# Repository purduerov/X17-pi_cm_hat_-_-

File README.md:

# X17-pi_cm_hat_-_-
Raspberry pi compute module 4 R&amp;D  board.

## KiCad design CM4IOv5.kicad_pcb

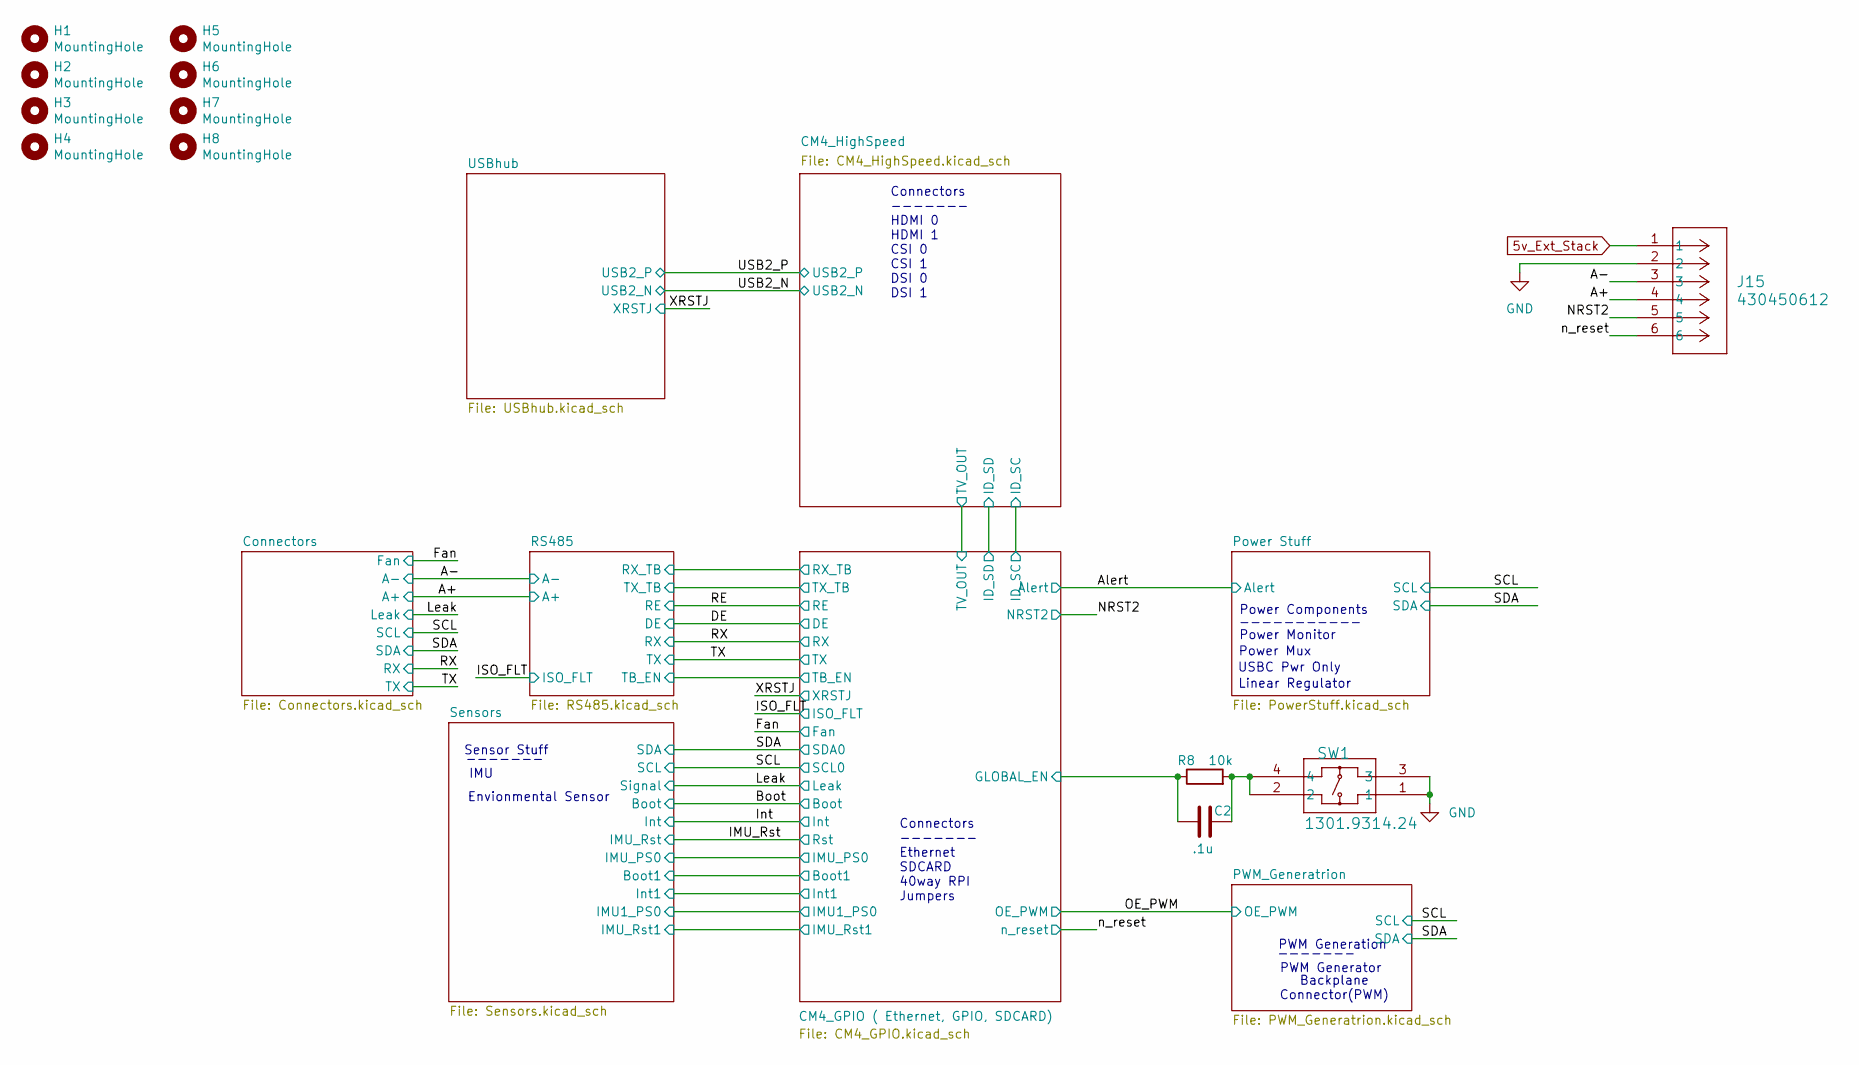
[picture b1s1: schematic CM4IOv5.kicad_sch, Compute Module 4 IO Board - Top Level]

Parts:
C2: .1u; C_0805_2012Metric
H1, H2, H3, H4, H5, H6, H7, H8: MountingHole; MountingHole_2.7mm_M2.5; Part Description M2.5 mounting hole
J15: 430450612; CON_430450612_MOL
R8: 10k; R_0805_2012Metric
SW1: 1301.9314.24; 1301.9314.24_SCH

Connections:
5v_Ext_Stack: J15.1; also elsewhere on the board
/A+: J15.4; also elsewhere on the board
/A-: J15.3; also elsewhere on the board
/CM4_GPIO ( Ethernet, GPIO, SDCARD)/GLOBAL_EN: C2.1, R8.1; also elsewhere on the board
/NRST2: J15.5; also elsewhere on the board
/n_reset: J15.6; also elsewhere on the board
GND: J15.2, SW1.1, SW1.3; also elsewhere on the board
unnamed: C2.2, R8.2, SW1.2, SW1.4

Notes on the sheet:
Power Mux
-----------
PWM Generation
Power Components
Envionmental Sensor
IMU
USBC Pwr Only
Sensor Stuff
-------
Connectors ------- Ethernet SDCARD 40way RPI Jumpers
Connectors ------- HDMI 0 HDMI 1 CSI 0 CSI 1 DSI 0 DSI 1
Backplane Connector(PWM)
PWM Generator
Linear Regulator
Power Monitor

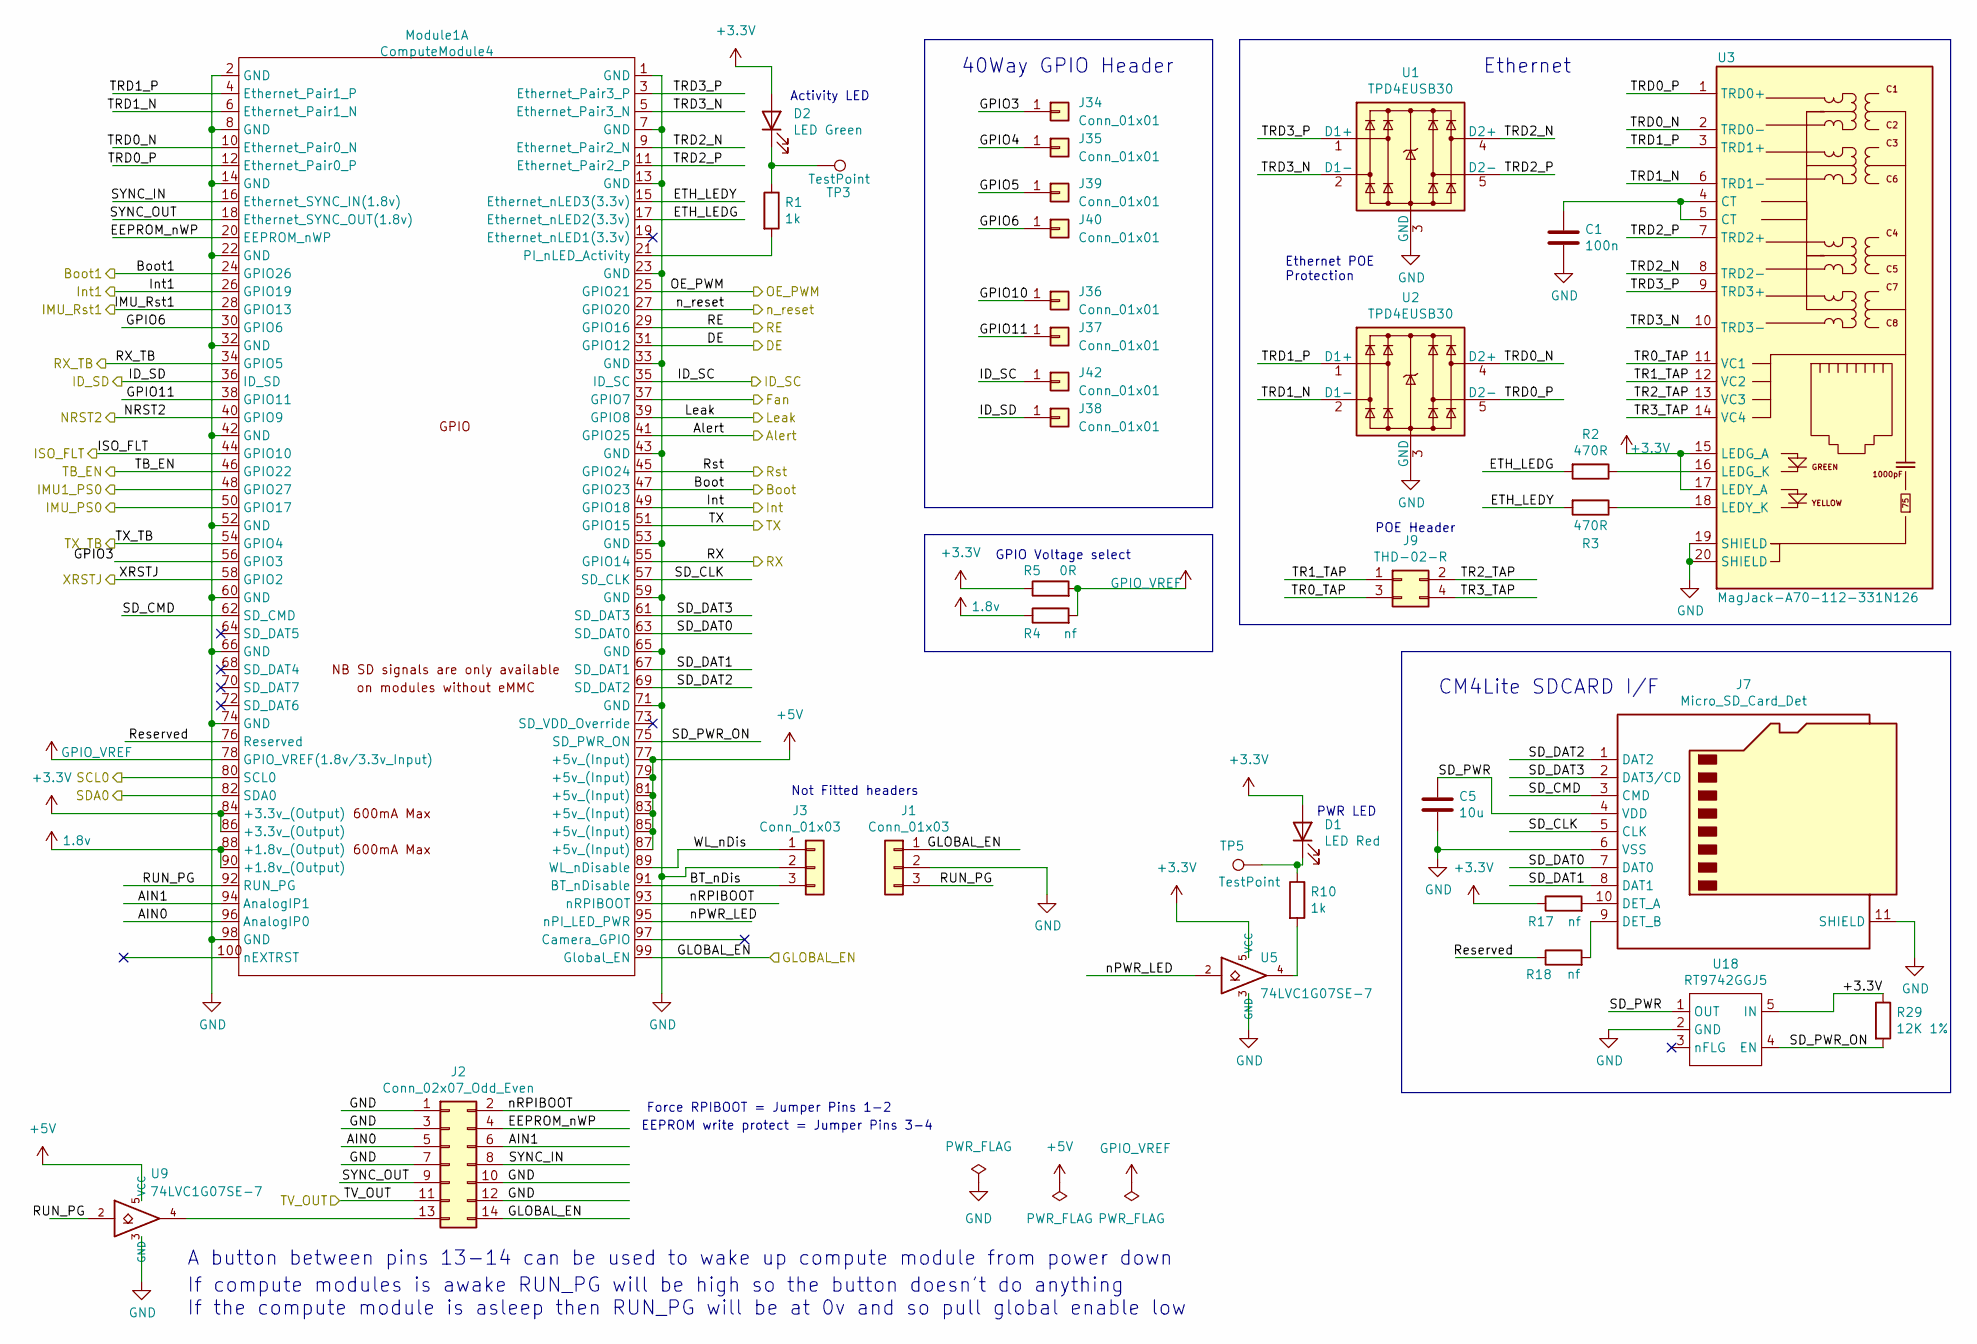
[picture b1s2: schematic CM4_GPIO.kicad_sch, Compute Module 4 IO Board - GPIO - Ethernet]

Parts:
C1: 100n; C_0805_2012Metric; Part Description 0.1uF 10% 16V Ceramic Capacitor X7R 040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
C5: 10u; C_0805_2012Metric; Part Description 10uF 10% 10V Ceramic Capacitor X7R 0805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
D1: LED Red; LED_0805_2012Metric; Part Description Red 620nm LED Indication - Discrete 2.2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
D2: LED Green; LED_0805_2012Metric; Part Description Green 572nm LED Indication - Discrete 2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
J1, J3: Conn_01x03; PinHeader_1x03_P2.54mm_Vertical; Part Description 3pin 0.1" connector
J2: Conn_02x07_Odd_Even; PinHeader_2x07_P2.54mm_Vertical; Part Description PinHeader_2x07_P2.54mm_Vertical
J7: Micro_SD_Card_Det; SDCARD_MOLEX_503398-1892; Part Description 9 (8 + 1) Position Card Connector micro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
J9: THD-02-R; PinHeader_2x02_P2.54mm_Vertical; Part Description PinHeader_2x02_P2.54mm_Vertical
J34, J35, J36, J37, J38, J39, J40, J42: Conn_01x01; PinHeader_1x01_P2.54mm_Vertical
Module1: ComputeModule4; Raspberry-Pi-4-Compute-Module; Part Description 100 Position Connector Receptacle, Cent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
R1, R10: 1k; R_0805_2012Metric; Part Description Resistor 1K M1005 1% 63mW
R2, R3: 470R; R_0805_2012Metric; Part Description Resistor 470R M1005 1% 63mW
R4: nf; R_0805_2012Metric
R5: 0R; R_0805_2012Metric; Part Description Resistor 0R M2012 5%
R17, R18: nf; R_0805_2012Metric; Part Description Resistor 1K M1005 1% 63mW
R29: 12K 1%; R_0805_2012Metric; Part Description Resistor 12K M1005 1% 63mW
TP3, TP5: TestPoint; TestPoint_Plated_Hole_D3.0mm
U1, U2: TPD4EUSB30; USON-10_2.5x1.0mm_P0.5mm; Part Description Quad TVS diode for high speed signals (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
U3: MagJack-A70-112-331N126; TRJG0926HENL; Part Description Gigabit Ethernet Magjack
U5, U9: 74LVC1G07SE-7; SOT-353_SC-70-5; Part Description Buffer, Non-Inverting 1 Element 1 Bit p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
U18: RT9742GGJ5; SOT-23-5; Part Description Power Switch/Driver 1:1 N-Channel 1A TS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

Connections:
1.8v: Module1.88 (+1.8v_(Output)), Module1.90 (+1.8v_(Output)), R4.1
+3.3V: D1.2 (A), D2.2 (A), Module1.84 (+3.3v_(Output)), Module1.86 (+3.3v_(Output)), R5.1, R17.1, R29.1, U3.15 (LEDG_A), U3.17 (LEDY_A), U5.5 (VCC), U18.5 (IN); also elsewhere on the board
+5V: Module1.77 (+5v_(Input)), Module1.79 (+5v_(Input)), Module1.81 (+5v_(Input)), Module1.83 (+5v_(Input)), Module1.85 (+5v_(Input)), Module1.87 (+5v_(Input)), U9.5 (VCC); also elsewhere on the board
/Alert: Module1.41 (GPIO25); also elsewhere on the board
/Boot: Module1.47 (GPIO23); also elsewhere on the board
/CM4_GPIO ( Ethernet, GPIO, SDCARD)/AIN0: J2.5, Module1.96 (AnalogIP0)
/CM4_GPIO ( Ethernet, GPIO, SDCARD)/AIN1: J2.6, Module1.94 (AnalogIP1)
/CM4_GPIO ( Ethernet, GPIO, SDCARD)/BT_nDis: J3.3, Module1.91 (BT_nDisable)
/CM4_GPIO ( Ethernet, GPIO, SDCARD)/Boot1: Module1.24 (GPIO26); also elsewhere on the board
/CM4_GPIO ( Ethernet, GPIO, SDCARD)/EEPROM_nWP: J2.4, Module1.20 (EEPROM_nWP)
/CM4_GPIO ( Ethernet, GPIO, SDCARD)/ETH_LEDG: Module1.17 (Ethernet_nLED2(3.3v)), R2.2
/CM4_GPIO ( Ethernet, GPIO, SDCARD)/ETH_LEDY: Module1.15 (Ethernet_nLED3(3.3v)), R3.2
/CM4_GPIO ( Ethernet, GPIO, SDCARD)/GLOBAL_EN: J1.1, J2.14, Module1.99 (Global_EN); also elsewhere on the board
/CM4_GPIO ( Ethernet, GPIO, SDCARD)/GPIO3: J34.1, Module1.56 (GPIO3)
/CM4_GPIO ( Ethernet, GPIO, SDCARD)/GPIO6: J40.1, Module1.30 (GPIO6)
/CM4_GPIO ( Ethernet, GPIO, SDCARD)/GPIO11: J37.1, Module1.38 (GPIO11)
/CM4_GPIO ( Ethernet, GPIO, SDCARD)/ID_SC: J42.1, Module1.35 (ID_SC); also elsewhere on the board
/CM4_GPIO ( Ethernet, GPIO, SDCARD)/ID_SD: J38.1, Module1.36 (ID_SD); also elsewhere on the board
/CM4_GPIO ( Ethernet, GPIO, SDCARD)/IMU1_PS0: Module1.48 (GPIO27); also elsewhere on the board
/CM4_GPIO ( Ethernet, GPIO, SDCARD)/IMU_PS0: Module1.50 (GPIO17); also elsewhere on the board
/CM4_GPIO ( Ethernet, GPIO, SDCARD)/IMU_Rst1: Module1.28 (GPIO13); also elsewhere on the board
/CM4_GPIO ( Ethernet, GPIO, SDCARD)/Int1: Module1.26 (GPIO19); also elsewhere on the board
/CM4_GPIO ( Ethernet, GPIO, SDCARD)/RUN_PG: J1.3, Module1.92 (RUN_PG), U9.2
/CM4_GPIO ( Ethernet, GPIO, SDCARD)/RX_TB: Module1.34 (GPIO5); also elsewhere on the board
/CM4_GPIO ( Ethernet, GPIO, SDCARD)/Reserved: Module1.76 (Reserved), R18.1
/CM4_GPIO ( Ethernet, GPIO, SDCARD)/SD_CLK: J7.5 (CLK), Module1.57 (SD_CLK)
/CM4_GPIO ( Ethernet, GPIO, SDCARD)/SD_CMD: J7.3 (CMD), Module1.62 (SD_CMD)
/CM4_GPIO ( Ethernet, GPIO, SDCARD)/SD_DAT0: J7.7 (DAT0), Module1.63 (SD_DAT0)
/CM4_GPIO ( Ethernet, GPIO, SDCARD)/SD_DAT1: J7.8 (DAT1), Module1.67 (SD_DAT1)
/CM4_GPIO ( Ethernet, GPIO, SDCARD)/SD_DAT2: J7.1 (DAT2), Module1.69 (SD_DAT2)
/CM4_GPIO ( Ethernet, GPIO, SDCARD)/SD_DAT3: J7.2 (DAT3/CD), Module1.61 (SD_DAT3)
/CM4_GPIO ( Ethernet, GPIO, SDCARD)/SD_PWR: C5.1, J7.4 (VDD), U18.1 (OUT)
/CM4_GPIO ( Ethernet, GPIO, SDCARD)/SD_PWR_ON: Module1.75 (SD_PWR_ON), R29.2, U18.4 (EN)
/CM4_GPIO ( Ethernet, GPIO, SDCARD)/SYNC_IN: J2.8, Module1.16 (Ethernet_SYNC_IN(1.8v))
/CM4_GPIO ( Ethernet, GPIO, SDCARD)/SYNC_OUT: J2.9, Module1.18 (Ethernet_SYNC_OUT(1.8v))
/CM4_GPIO ( Ethernet, GPIO, SDCARD)/TB_EN: Module1.46 (GPIO22); also elsewhere on the board
/CM4_GPIO ( Ethernet, GPIO, SDCARD)/TR0_TAP: J9.3, U3.11 (VC1)
/CM4_GPIO ( Ethernet, GPIO, SDCARD)/TR1_TAP: J9.1, U3.12 (VC2)
/CM4_GPIO ( Ethernet, GPIO, SDCARD)/TR2_TAP: J9.2, U3.13 (VC3)
/CM4_GPIO ( Ethernet, GPIO, SDCARD)/TR3_TAP: J9.4, U3.14 (VC4)
/CM4_GPIO ( Ethernet, GPIO, SDCARD)/TRD0_N: Module1.10 (Ethernet_Pair0_N), U2.4 (D2+), U2.7, U3.2 (TRD0-)
/CM4_GPIO ( Ethernet, GPIO, SDCARD)/TRD0_P: Module1.12 (Ethernet_Pair0_P), U2.5 (D2-), U2.6, U3.1 (TRD0+)
/CM4_GPIO ( Ethernet, GPIO, SDCARD)/TRD1_N: Module1.6 (Ethernet_Pair1_N), U2.2 (D1-), U2.9, U3.6 (TRD1-)
/CM4_GPIO ( Ethernet, GPIO, SDCARD)/TRD1_P: Module1.4 (Ethernet_Pair1_P), U2.1 (D1+), U2.10, U3.3 (TRD1+)
/CM4_GPIO ( Ethernet, GPIO, SDCARD)/TRD2_N: Module1.9 (Ethernet_Pair2_N), U1.4 (D2+), U1.7, U3.8 (TRD2-)
/CM4_GPIO ( Ethernet, GPIO, SDCARD)/TRD2_P: Module1.11 (Ethernet_Pair2_P), U1.5 (D2-), U1.6, U3.7 (TRD2+)
/CM4_GPIO ( Ethernet, GPIO, SDCARD)/TRD3_N: Module1.5 (Ethernet_Pair3_N), U1.2 (D1-), U1.9, U3.10 (TRD3-)
/CM4_GPIO ( Ethernet, GPIO, SDCARD)/TRD3_P: Module1.3 (Ethernet_Pair3_P), U1.1 (D1+), U1.10, U3.9 (TRD3+)
/CM4_GPIO ( Ethernet, GPIO, SDCARD)/TV_OUT: J2.11; also elsewhere on the board
/CM4_GPIO ( Ethernet, GPIO, SDCARD)/TX_TB: Module1.54 (GPIO4); also elsewhere on the board
/CM4_GPIO ( Ethernet, GPIO, SDCARD)/WL_nDis: J3.1, Module1.89 (WL_nDisable)
/CM4_GPIO ( Ethernet, GPIO, SDCARD)/nPWR_LED: Module1.95 (nPI_LED_PWR), U5.2
/CM4_GPIO ( Ethernet, GPIO, SDCARD)/nRPIBOOT: J2.2, Module1.93 (nRPIBOOT)
/DE: Module1.31 (GPIO12); also elsewhere on the board
/Fan: Module1.37 (GPIO7); also elsewhere on the board
/IMU_Rst: Module1.45 (GPIO24); also elsewhere on the board
/ISO_FLT: Module1.44 (GPIO10); also elsewhere on the board
/Int: Module1.49 (GPIO18); also elsewhere on the board
/Leak: Module1.39 (GPIO8); also elsewhere on the board
/NRST2: Module1.40 (GPIO9); also elsewhere on the board
/OE_PWM: Module1.25 (GPIO21); also elsewhere on the board
/RE: Module1.29 (GPIO16); also elsewhere on the board
/RX: Module1.55 (GPIO14); also elsewhere on the board
/SCL: Module1.80 (SCL0); also elsewhere on the board
/SDA: Module1.82 (SDA0); also elsewhere on the board
/TX: Module1.51 (GPIO15); also elsewhere on the board
/XRSTJ: Module1.58 (GPIO2); also elsewhere on the board
/n_reset: Module1.27 (GPIO20); also elsewhere on the board
GND: C1.2, C5.2, J1.2, J2.1, J2.3, J2.7, J2.10, J2.12, J3.2, J7.6 (VSS), J7.11 (SHIELD), Module1.1 (GND), Module1.2 (GND), Module1.7 (GND), Module1.8 (GND), Module1.13 (GND), Module1.14 (GND), Module1.22 (GND), Module1.23 (GND), Module1.32 (GND), Module1.33 (GND), Module1.42 (GND), Module1.43 (GND), Module1.52 (GND), Module1.53 (GND), Module1.59 (GND), Module1.60 (GND), Module1.65 (GND), Module1.66 (GND), Module1.71 (GND), Module1.74 (GND), Module1.98 (GND), U1.3 (GND), U1.8 (GND), U2.3 (GND), U2.8 (GND), U3.19 (SHIELD), U3.20 (SHIELD), U5.3 (GND), U9.3 (GND), U18.2 (GND); also elsewhere on the board
GPIO_VREF: Module1.78 (GPIO_VREF(1.8v/3.3v_Input)), R4.2, R5.2; also elsewhere on the board
unnamed: C1.1, U3.4 (CT), U3.5 (CT)
unnamed: D1.1 (K), R10.1, TP5.1
unnamed: D2.1 (K), R1.1, TP3.1
unnamed: J2.13, U9.4
unnamed: J7.10 (DET_A), R17.2
unnamed: J7.9 (DET_B), R18.2
unnamed: Module1.21 (PI_nLED_Activity), R1.2
unnamed: R10.2, U5.4
unnamed: R2.1, U3.16 (LEDG_K)
unnamed: R3.1, U3.18 (LEDY_K)

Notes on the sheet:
PWR LED
Ethernet POE Protection
40Way GPIO Header
CM4Lite SDCARD I/F
GPIO Voltage select
Ethernet
Activity LED
EEPROM write protect = Jumper Pins 3-4
Not Fitted headers
A button between pins 13-14 can be used to wake up compute module from power down
If compute modules is awake RUN_PG will be high so the button doesn't do anything If the compute module is asleep then RUN_PG will be at 0v and so pull global enable low
Force RPIBOOT = Jumper Pins 1-2
POE Header

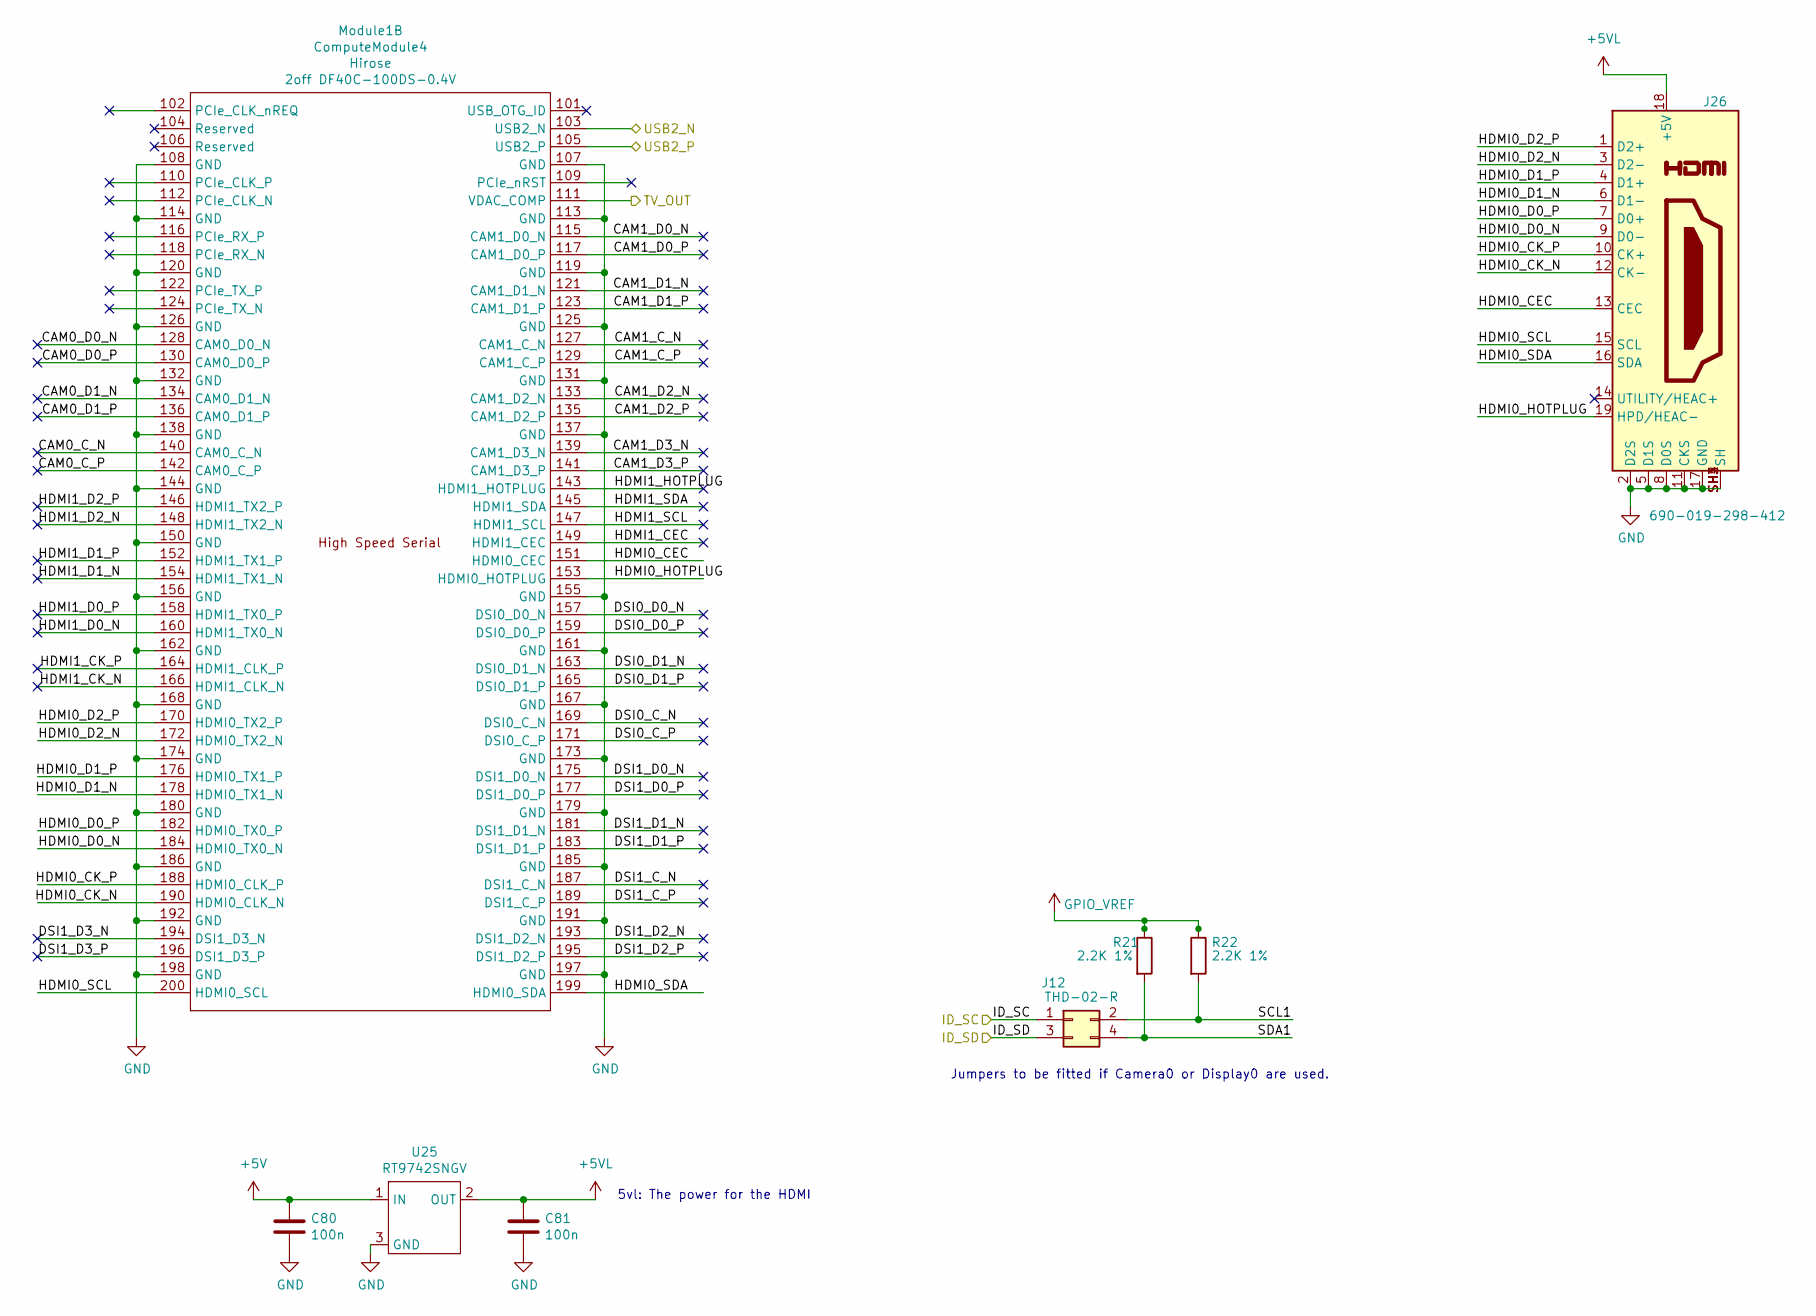
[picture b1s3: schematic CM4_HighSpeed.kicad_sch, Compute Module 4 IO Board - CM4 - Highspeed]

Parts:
C80, C81: 100n; C_0805_2012Metric; Part Description 0.1uF 10% 16V Ceramic Capacitor X7R 040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
J12: THD-02-R; PinHeader_2x02_P2.54mm_Vertical; Part Description PinHeader_2x02_P2.54mm_Vertical
J26: 690-019-298-412; EDAC 690-019-298-412; Part Description HDMI Connector, Right Angle, 19 Contact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
Module1: ComputeModule4; Raspberry-Pi-4-Compute-Module; Part Description 100 Position Connector Receptacle, Cent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
R21, R22: 2.2K 1%; R_0805_2012Metric; Part Description Resistor 2.2K M1005 1% 63mW
U25: RT9742SNGV; SOT-23; Part Description Power Switch/Driver 1:1 N-Channel 500mA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

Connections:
+5V: C80.1, U25.1 (IN); also elsewhere on the board
+5VL: C81.1, J26.18 (+5V), U25.2 (OUT)
/CM4_GPIO ( Ethernet, GPIO, SDCARD)/ID_SC: J12.1; also elsewhere on the board
/CM4_GPIO ( Ethernet, GPIO, SDCARD)/ID_SD: J12.3; also elsewhere on the board
/CM4_GPIO ( Ethernet, GPIO, SDCARD)/TV_OUT: Module1.111 (VDAC_COMP); also elsewhere on the board
/CM4_HighSpeed/CAM0_C_N: Module1.140 (CAM0_C_N)
/CM4_HighSpeed/CAM0_C_P: Module1.142 (CAM0_C_P)
/CM4_HighSpeed/CAM0_D0_N: Module1.128 (CAM0_D0_N)
/CM4_HighSpeed/CAM0_D0_P: Module1.130 (CAM0_D0_P)
/CM4_HighSpeed/CAM0_D1_N: Module1.134 (CAM0_D1_N)
/CM4_HighSpeed/CAM0_D1_P: Module1.136 (CAM0_D1_P)
/CM4_HighSpeed/CAM1_C_N: Module1.127 (CAM1_C_N)
/CM4_HighSpeed/CAM1_C_P: Module1.129 (CAM1_C_P)
/CM4_HighSpeed/CAM1_D0_N: Module1.115 (CAM1_D0_N)
/CM4_HighSpeed/CAM1_D0_P: Module1.117 (CAM1_D0_P)
/CM4_HighSpeed/CAM1_D1_N: Module1.121 (CAM1_D1_N)
/CM4_HighSpeed/CAM1_D1_P: Module1.123 (CAM1_D1_P)
/CM4_HighSpeed/CAM1_D2_N: Module1.133 (CAM1_D2_N)
/CM4_HighSpeed/CAM1_D2_P: Module1.135 (CAM1_D2_P)
/CM4_HighSpeed/CAM1_D3_N: Module1.139 (CAM1_D3_N)
/CM4_HighSpeed/CAM1_D3_P: Module1.141 (CAM1_D3_P)
/CM4_HighSpeed/DSI0_C_N: Module1.169 (DSI0_C_N)
/CM4_HighSpeed/DSI0_C_P: Module1.171 (DSI0_C_P)
/CM4_HighSpeed/DSI0_D0_N: Module1.157 (DSI0_D0_N)
/CM4_HighSpeed/DSI0_D0_P: Module1.159 (DSI0_D0_P)
/CM4_HighSpeed/DSI0_D1_N: Module1.163 (DSI0_D1_N)
/CM4_HighSpeed/DSI0_D1_P: Module1.165 (DSI0_D1_P)
/CM4_HighSpeed/DSI1_C_N: Module1.187 (DSI1_C_N)
/CM4_HighSpeed/DSI1_C_P: Module1.189 (DSI1_C_P)
/CM4_HighSpeed/DSI1_D0_N: Module1.175 (DSI1_D0_N)
/CM4_HighSpeed/DSI1_D0_P: Module1.177 (DSI1_D0_P)
/CM4_HighSpeed/DSI1_D1_N: Module1.181 (DSI1_D1_N)
/CM4_HighSpeed/DSI1_D1_P: Module1.183 (DSI1_D1_P)
/CM4_HighSpeed/DSI1_D2_N: Module1.193 (DSI1_D2_N)
/CM4_HighSpeed/DSI1_D2_P: Module1.195 (DSI1_D2_P)
/CM4_HighSpeed/DSI1_D3_N: Module1.194 (DSI1_D3_N)
/CM4_HighSpeed/DSI1_D3_P: Module1.196 (DSI1_D3_P)
/CM4_HighSpeed/HDMI0_CEC: J26.13 (CEC), Module1.151 (HDMI0_CEC)
/CM4_HighSpeed/HDMI0_CK_N: J26.12 (CK-), Module1.190 (HDMI0_CLK_N)
/CM4_HighSpeed/HDMI0_CK_P: J26.10 (CK+), Module1.188 (HDMI0_CLK_P)
/CM4_HighSpeed/HDMI0_D0_N: J26.9 (D0-), Module1.184 (HDMI0_TX0_N)
/CM4_HighSpeed/HDMI0_D0_P: J26.7 (D0+), Module1.182 (HDMI0_TX0_P)
/CM4_HighSpeed/HDMI0_D1_N: J26.6 (D1-), Module1.178 (HDMI0_TX1_N)
/CM4_HighSpeed/HDMI0_D1_P: J26.4 (D1+), Module1.176 (HDMI0_TX1_P)
/CM4_HighSpeed/HDMI0_D2_N: J26.3 (D2-), Module1.172 (HDMI0_TX2_N)
/CM4_HighSpeed/HDMI0_D2_P: J26.1 (D2+), Module1.170 (HDMI0_TX2_P)
/CM4_HighSpeed/HDMI0_HOTPLUG: J26.19 (HPD/HEAC-), Module1.153 (HDMI0_HOTPLUG)
/CM4_HighSpeed/HDMI0_SCL: J26.15 (SCL), Module1.200 (HDMI0_SCL)
/CM4_HighSpeed/HDMI0_SDA: J26.16 (SDA), Module1.199 (HDMI0_SDA)
/CM4_HighSpeed/HDMI1_CEC: Module1.149 (HDMI1_CEC)
/CM4_HighSpeed/HDMI1_CK_N: Module1.166 (HDMI1_CLK_N)
/CM4_HighSpeed/HDMI1_CK_P: Module1.164 (HDMI1_CLK_P)
/CM4_HighSpeed/HDMI1_D0_N: Module1.160 (HDMI1_TX0_N)
/CM4_HighSpeed/HDMI1_D0_P: Module1.158 (HDMI1_TX0_P)
/CM4_HighSpeed/HDMI1_D1_N: Module1.154 (HDMI1_TX1_N)
/CM4_HighSpeed/HDMI1_D1_P: Module1.152 (HDMI1_TX1_P)
/CM4_HighSpeed/HDMI1_D2_N: Module1.148 (HDMI1_TX2_N)
/CM4_HighSpeed/HDMI1_D2_P: Module1.146 (HDMI1_TX2_P)
/CM4_HighSpeed/HDMI1_HOTPLUG: Module1.143 (HDMI1_HOTPLUG)
/CM4_HighSpeed/HDMI1_SCL: Module1.147 (HDMI1_SCL)
/CM4_HighSpeed/HDMI1_SDA: Module1.145 (HDMI1_SDA)
/CM4_HighSpeed/SCL1: J12.2, R22.2
/CM4_HighSpeed/SDA1: J12.4, R21.2
/USB2_N: Module1.103 (USB2_N); also elsewhere on the board
/USB2_P: Module1.105 (USB2_P); also elsewhere on the board
GND: C80.2, C81.2, J26.2 (D2S), J26.5 (D1S), J26.8 (D0S), J26.11 (CKS), J26.17 (GND), J26.SH1 (SH), J26.SH2 (SH), J26.SH3 (SH), J26.SH4 (SH), Module1.107 (GND), Module1.108 (GND), Module1.113 (GND), Module1.114 (GND), Module1.119 (GND), Module1.120 (GND), Module1.125 (GND), Module1.126 (GND), Module1.131 (GND), Module1.132 (GND), Module1.137 (GND), Module1.138 (GND), Module1.144 (GND), Module1.150 (GND), Module1.155 (GND), Module1.156 (GND), Module1.161 (GND), Module1.162 (GND), Module1.167 (GND), Module1.168 (GND), Module1.173 (GND), Module1.174 (GND), Module1.179 (GND), Module1.180 (GND), Module1.185 (GND), Module1.186 (GND), Module1.191 (GND), Module1.192 (GND), Module1.197 (GND), Module1.198 (GND), U25.3 (GND); also elsewhere on the board
GPIO_VREF: R21.1, R22.1; also elsewhere on the board

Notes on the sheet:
Jumpers to be fitted if Camera0 or Display0 are used.
5vl: The power for the HDMI

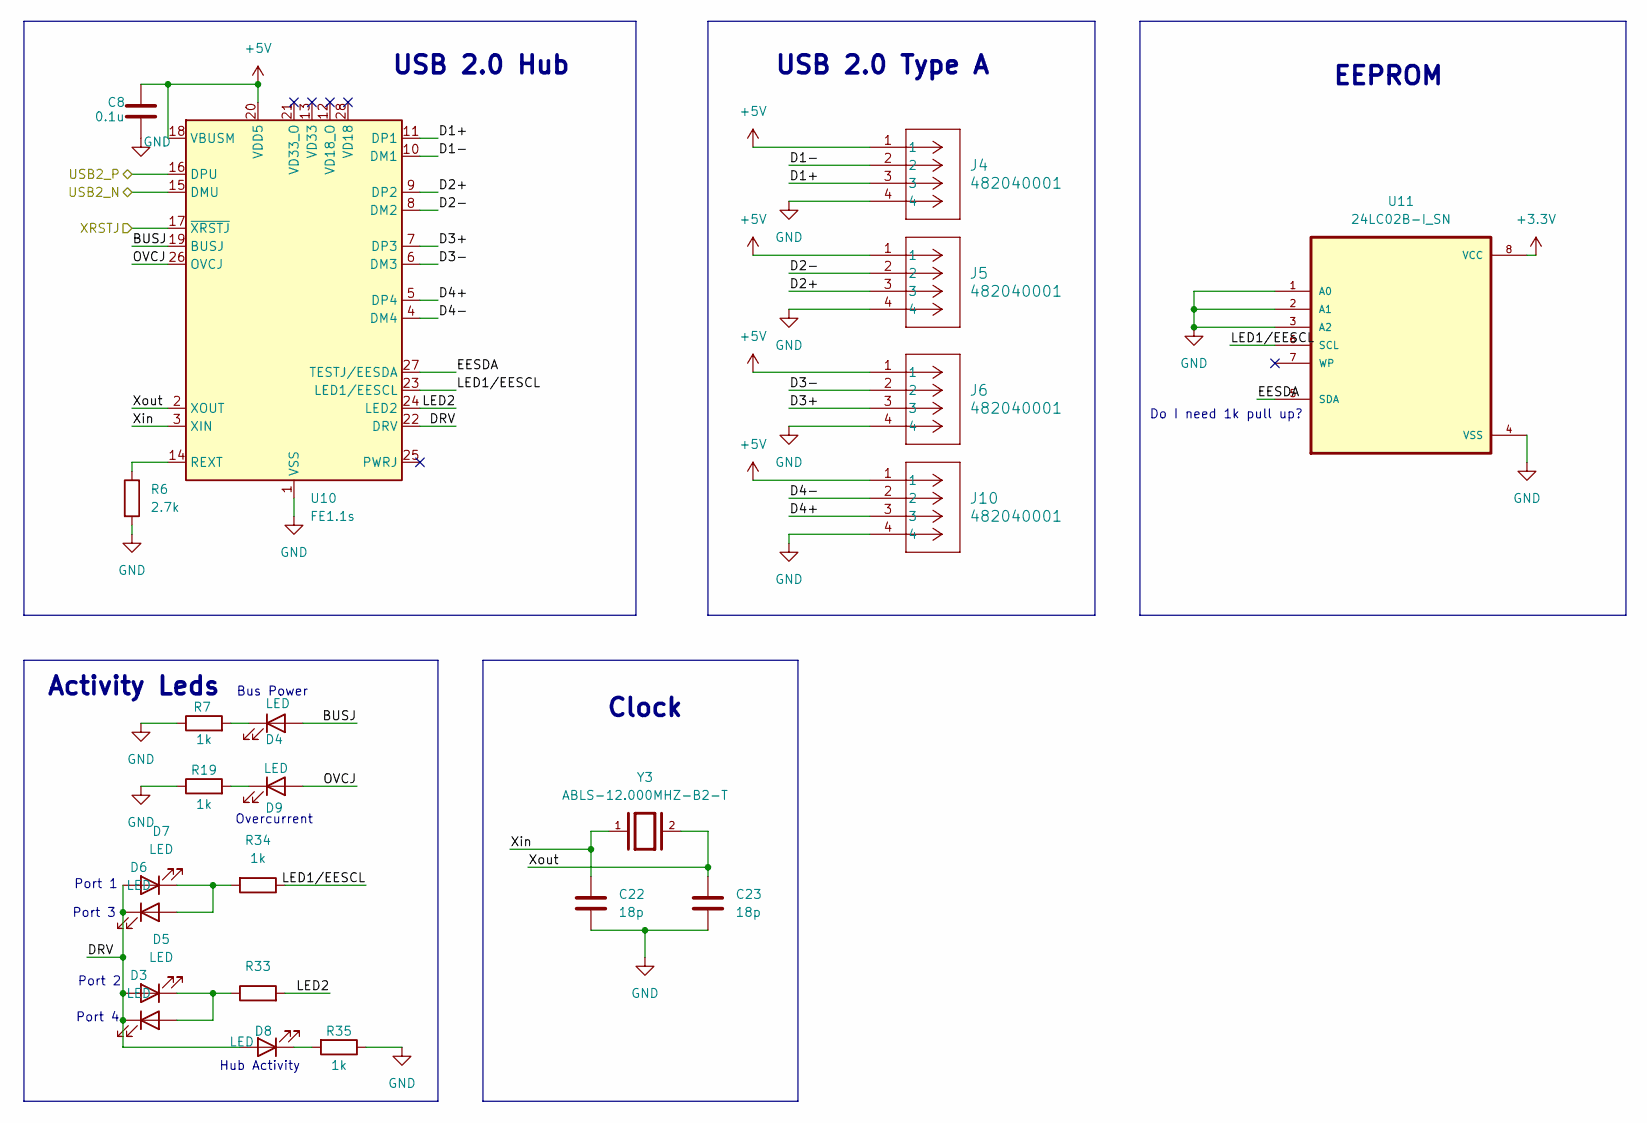
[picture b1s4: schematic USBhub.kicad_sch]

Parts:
C8: 0.1u; C_0805_2012Metric
C22, C23: 18p; C_0805_2012Metric
D3, D4, D5, D6, D7, D8, D9: LED; LED_0805_2012Metric
J4, J5, J6, J10: 482040001; CONN_48204-0001_MOL
R6: 2.7k; R_0805_2012Metric
R7, R19, R33, R34, R35: 1k; R_0805_2012Metric
U10: FE1.1s; SSOP-28_3.9x9.9mm_P0.635mm
U11: 24LC02B-I_SN; SOIC127P600X175-8N
Y3: ABLS-12.000MHZ-B2-T; XTAL_ABLS-12.000MHZ-B2-T; PARTREV 02.16.2021

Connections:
+3.3V: U11.8 (VCC); also elsewhere on the board
+5V: C8.1, J4.1, J5.1, J6.1, J10.1, U10.18 (VBUSM), U10.20 (VDD5); also elsewhere on the board
/USB2_N: U10.15 (DMU); also elsewhere on the board
/USB2_P: U10.16 (DPU); also elsewhere on the board
/USBhub/BUSJ: D4.2 (A), U10.19 (BUSJ)
/USBhub/D1+: J4.3, U10.11 (DP1)
/USBhub/D1-: J4.2, U10.10 (DM1)
/USBhub/D2+: J5.3, U10.9 (DP2)
/USBhub/D2-: J5.2, U10.8 (DM2)
/USBhub/D3+: J6.3, U10.7 (DP3)
/USBhub/D3-: J6.2, U10.6 (DM3)
/USBhub/D4+: J10.3, U10.5 (DP4)
/USBhub/D4-: J10.2, U10.4 (DM4)
/USBhub/DRV: D3.1 (K), D5.2 (A), D6.1 (K), D7.2 (A), D8.2 (A), U10.22 (DRV)
/USBhub/EESDA: U10.27 (TESTJ/EESDA), U11.5 (SDA)
/USBhub/LED1/EESCL: R34.1, U10.23 (LED1/EESCL), U11.6 (SCL)
/USBhub/LED2: R33.2, U10.24 (LED2)
/USBhub/OVCJ: D9.2 (A), U10.26 (OVCJ)
/USBhub/Xin: C22.2, U10.3 (XIN), Y3.1
/USBhub/Xout: C23.1, U10.2 (XOUT), Y3.2
/XRSTJ: U10.17 (~XRSTJ); also elsewhere on the board
GND: C8.2, C22.1, C23.2, J4.4, J5.4, J6.4, J10.4, R6.2, R7.1, R19.1, R35.1, U10.1 (VSS), U11.1 (A0), U11.2 (A1), U11.3 (A2), U11.4 (VSS); also elsewhere on the board
unnamed: D3.2 (A), D5.1 (K), R33.1
unnamed: D4.1 (K), R7.2
unnamed: D6.2 (A), D7.1 (K), R34.2
unnamed: D8.1 (K), R35.2
unnamed: D9.1 (K), R19.2
unnamed: R6.1, U10.14 (REXT)

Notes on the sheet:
Hub Activity
Clock
Bus Power
Port 1
Port 4
USB 2.0 Type A
USB 2.0 Hub
EEPROM
Do I need 1k pull up?
Activity Leds
Overcurrent
Port 3
Port 2

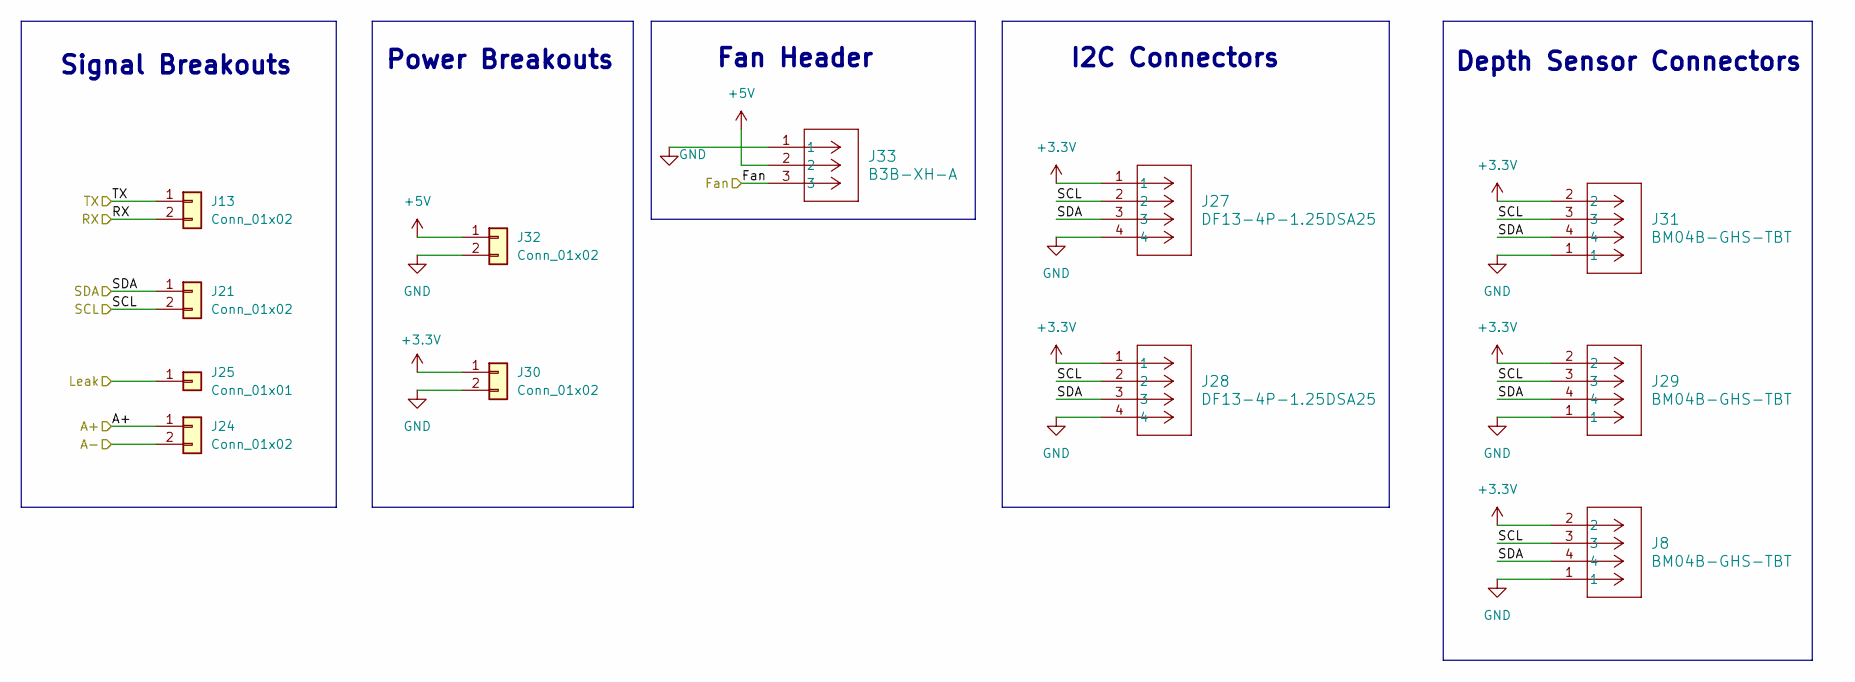
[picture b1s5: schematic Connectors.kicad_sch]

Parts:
J8, J29, J31: BM04B-GHS-TBT; CONN_BM04B-GHS-TBT_JST
J13, J21, J24, J30, J32: Conn_01x02; PinHeader_1x02_P2.54mm_Vertical
J25: Conn_01x01; PinHeader_1x01_P2.54mm_Vertical
J27, J28: DF13-4P-1.25DSA25; CONN4_DF13-4P_HIR
J33: B3B-XH-A; CONN_B3B-XH-A_JST

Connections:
+3.3V: J8.2, J27.1, J28.1, J29.2, J30.1, J31.2; also elsewhere on the board
+5V: J32.1, J33.2; also elsewhere on the board
/A+: J24.1; also elsewhere on the board
/A-: J24.2; also elsewhere on the board
/Fan: J33.3; also elsewhere on the board
/Leak: J25.1; also elsewhere on the board
/RX: J13.2; also elsewhere on the board
/SCL: J8.3, J21.2, J27.2, J28.2, J29.3, J31.3; also elsewhere on the board
/SDA: J8.4, J21.1, J27.3, J28.3, J29.4, J31.4; also elsewhere on the board
/TX: J13.1; also elsewhere on the board
GND: J8.1, J27.4, J28.4, J29.1, J30.2, J31.1, J32.2, J33.1; also elsewhere on the board

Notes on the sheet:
Fan Header
Depth Sensor Connectors
I2C Connectors
Power Breakouts
Signal Breakouts

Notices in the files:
CM4_GPIO.kicad_sch:
© 2020-2022 Raspberry Pi Ltd (formerly Raspberry Pi (Trading) Ltd.)
